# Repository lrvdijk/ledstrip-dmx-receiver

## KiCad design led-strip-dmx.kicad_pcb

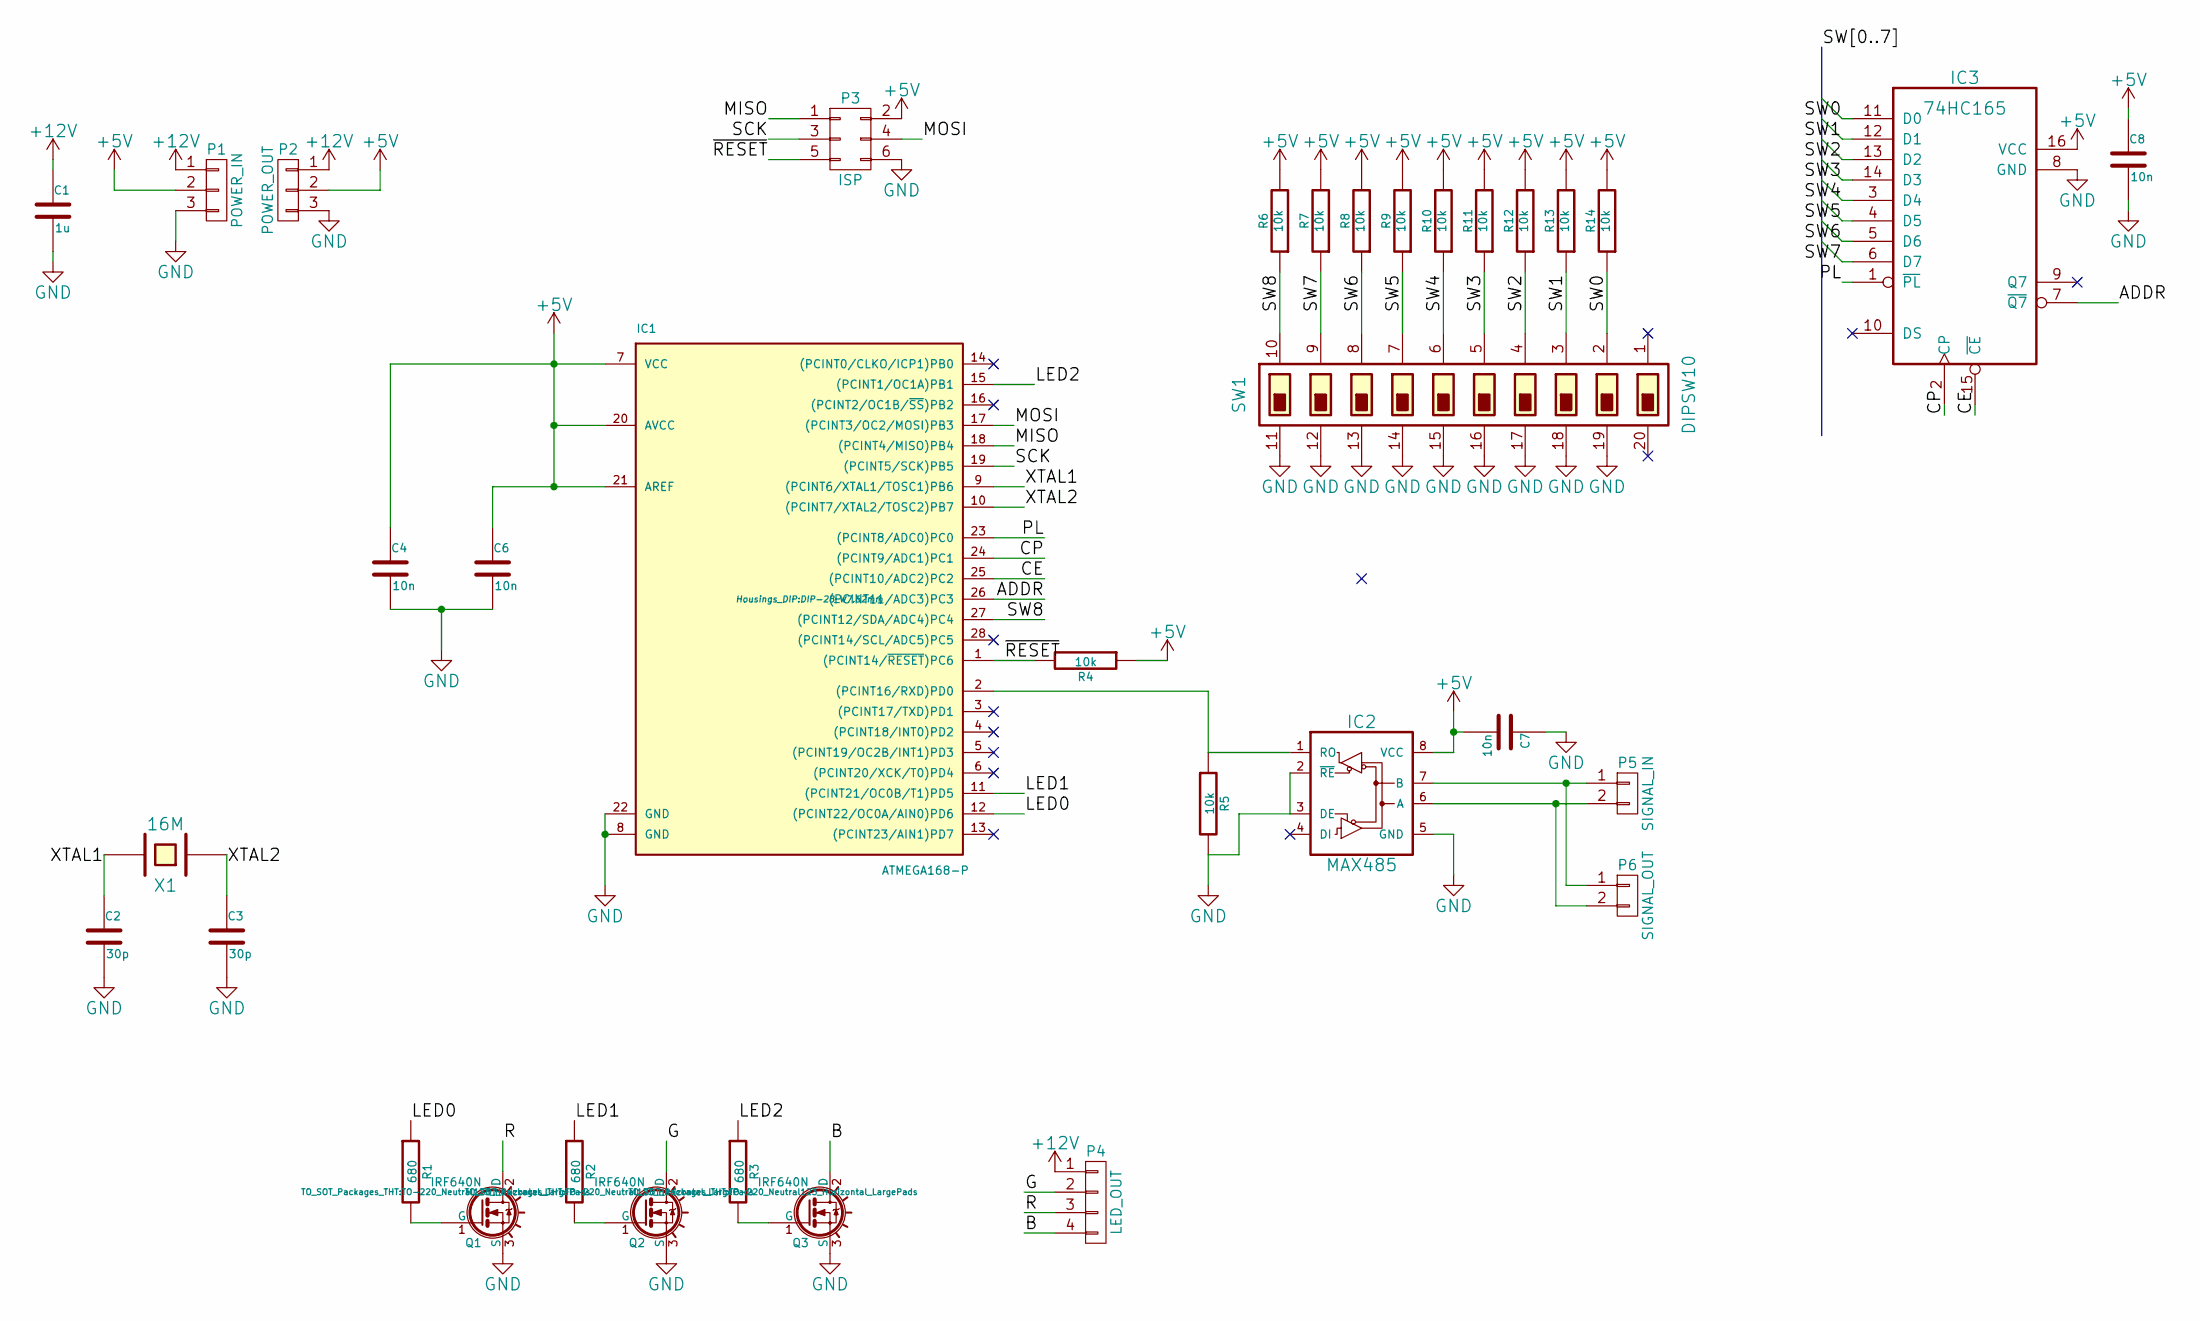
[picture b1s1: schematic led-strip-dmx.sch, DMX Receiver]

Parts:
C1: 1u; Elko_vert_11.2x6.3mm_RM2.5
C2, C3: 30p; C_Disc_D3_P2.5
C4, C6, C7, C8: 10n; C_Disc_D3_P2.5
IC1: ATMEGA168-P; DIP-28_W7.62mm
IC2: MAX485; DIP-8_W7.62mm
IC3: 74HC165; DIP-16_W7.62mm
P1: POWER_IN; Pin_Header_Straight_1x03
P2: POWER_OUT; Pin_Header_Straight_1x03
P3: ISP; Pin_Header_Straight_2x03
P4: LED_OUT; pin_strip_2mm_4
P5: SIGNAL_IN; Pin_Header_Straight_2x01
P6: SIGNAL_OUT; Pin_Header_Straight_2x01
Q1, Q2, Q3: IRF640N; TO-220_Neutral123_Horizontal_LargePads
R1, R2, R3: 680; Resistor_Horizontal_RM10mm
R4, R5, R6, R7, R8, R9, R10, R11, R12, R13, R14: 10k; Resistor_Horizontal_RM10mm
SW1: DIPSW10; DIP-20_W7.62mm
X1: 16M; HC-49V

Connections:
+5V: C4.1, C6.1, C7.2, C8.1, IC1.7 (VCC), IC1.20 (AVCC), IC1.21 (AREF), IC2.8 (VCC), IC3.16 (VCC), P1.2, P2.2, P3.2, R4.1, R6.2, R7.2, R8.2, R9.2, R10.2, R11.2, R12.2, R13.2, R14.2
+12V: C1.1, P1.1, P2.1, P4.1
/ADDR: IC1.26 ((PCINT11/ADC3)PC3), IC3.7 (~Q7)
/B: P4.4, Q3.2 (D)
/CE: IC1.25 ((PCINT10/ADC2)PC2), IC3.15 (~CE)
/CP: IC1.24 ((PCINT9/ADC1)PC1), IC3.2 (CP)
/G: P4.2, Q2.2 (D)
/LED0: IC1.12 ((PCINT22/OC0A/AIN0)PD6), R1.1
/LED1: IC1.11 ((PCINT21/OC0B/T1)PD5), R2.1
/LED2: IC1.15 ((PCINT1/OC1A)PB1), R3.1
/MISO: IC1.18 ((PCINT4/MISO)PB4), P3.1
/MOSI: IC1.17 ((PCINT3/OC2/MOSI)PB3), P3.4
/PL: IC1.23 ((PCINT8/ADC0)PC0), IC3.1 (~PL)
/R: P4.3, Q1.2 (D)
/SCK: IC1.19 ((PCINT5/SCK)PB5), P3.3
/SW0: IC3.11 (D0), R14.1, SW1.2
/SW1: IC3.12 (D1), R13.1, SW1.3
/SW2: IC3.13 (D2), R12.1, SW1.4
/SW3: IC3.14 (D3), R11.1, SW1.5
/SW4: IC3.3 (D4), R10.1, SW1.6
/SW5: IC3.4 (D5), R9.1, SW1.7
/SW6: IC3.5 (D6), R8.1, SW1.8
/SW7: IC3.6 (D7), R7.1, SW1.9
/SW8: IC1.27 ((PCINT12/SDA/ADC4)PC4), R6.1, SW1.10
/XTAL1: C2.1, IC1.9 ((PCINT6/XTAL1/TOSC1)PB6), X1.2
/XTAL2: C3.1, IC1.10 ((PCINT7/XTAL2/TOSC2)PB7), X1.1
/~RESET: IC1.1 ((PCINT14/~RESET~)PC6), P3.5, R4.2
GND: C1.2, C2.2, C3.2, C4.2, C6.2, C7.1, C8.2, IC1.8 (GND), IC1.22 (GND), IC2.2 (~RE), IC2.3 (DE), IC2.5 (GND), IC3.8 (GND), P1.3, P2.3, P3.6, Q1.3 (S), Q2.3 (S), Q3.3 (S), R5.2, SW1.11, SW1.12, SW1.13, SW1.14, SW1.15, SW1.16, SW1.17, SW1.18, SW1.19
unnamed: IC1.2 ((PCINT16/RXD)PD0), IC2.1 (RO), R5.1
unnamed: IC2.6 (A), P5.2, P6.2
unnamed: IC2.7 (B), P5.1, P6.1
unnamed: Q1.1 (G), R1.2
unnamed: Q2.1 (G), R2.2
unnamed: Q3.1 (G), R3.2

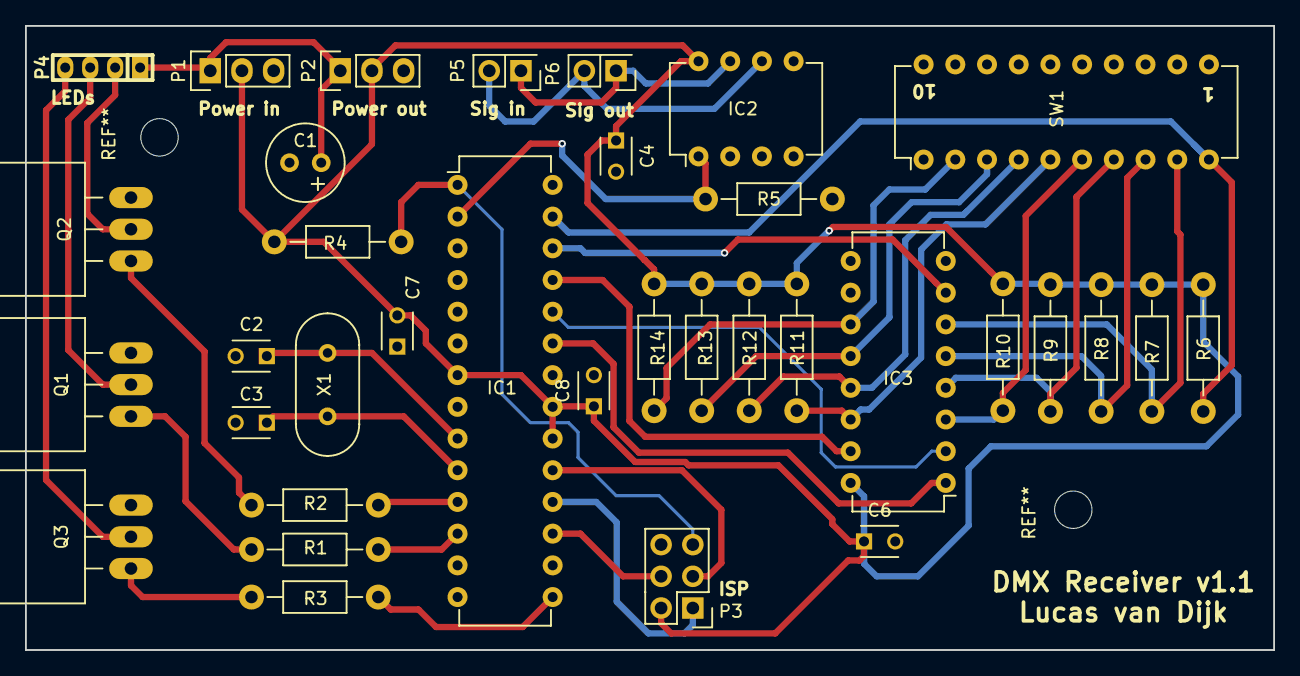
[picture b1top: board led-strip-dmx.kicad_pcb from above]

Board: 2 copper layers, 100.0 x 50.0 mm, 35 parts (0 on the bottom side), 34 nets.

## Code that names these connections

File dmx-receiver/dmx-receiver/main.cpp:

#include <stdint.h>
#include <avr/io.h>
#include <avr/interrupt.h>

#include "74hc165.h"
#include "dmx.h"

#define BAUD 250000
#define DMX_UBBR F_CPU/16/BAUD-1

// Four channels: master, R, G, B
#define DMX_CHANNELS 4

volatile uint16_t dmxAddress = 0;
volatile DmxState dmxState = IDLE;
volatile uint8_t dmxData[DMX_CHANNELS];

volatile uint8_t red = 0;
volatile uint8_t green = 0;
volatile uint8_t blue = 0;


int main() {

    // Temporarily disable interrupts
    cli();

    // Configure PWM ports as output
    DDRB = (1 << PB1);
    DDRD = (1 << PD5) | (1 << PD6);

    // 74HC165 control lines as output
    DDRC = (1 << PC0) | (1 << PC1) | (1 << PC2);

    // We use the two timers for PWM outputs
    // Setup timer 0
    // 8 bit fast PWM, non-inverting output on OC0A and OC0B, clock pre-scaler of 8
    // Enable overflow interrupt
    TCCR0A = (1 << COM0A1) | (1 << COM0B1) | (1 << WGM01) | (1 << WGM00);
    TCCR0B = (1 << CS01);
    TIMSK0 = (1 << TOIE0);

    // Setup timer 1 (16 bit timer)
    // 8 bit fast PWM, non-inverting output on OC1A, clock pre-scaler of 8
    // Enable overflow interrupt
    TCCR1A = (1 << COM1A1) | (1 << WGM12) | (1 << WGM10);
    TCCR1B = (1 << CS11);
    TIMSK1 = (1 << TOIE1);


    for(int i = 0; i < DMX_CHANNELS; i++) {
        dmxData[i] = 0;
    }

    // Initialize UART for DMX receiver
    init_uart(DMX_UBBR);

    // Enable interrupts again
    sei();
    uint8_t switch1 = 0;
    uint8_t switches = 0;

    while(true) {
        load_data_74hc165();
        switch1 = (PINC & (1 << PC4)) == 0 ? 1 : 0;
        switches = read_byte_74hc165();

        dmxAddress = (switches << 1) | switch1;

        // Calculate the pulse widths
        uint8_t master = dmxData[0];
        if(master < 255) {
            red = ((uint16_t) dmxData[1] * master) / 255;
            green = ((uint16_t) dmxData[2] * master) / 255;
            blue = ((uint16_t) dmxData[3] * master) / 255;
        } else {
            red = dmxData[1];
            green = dmxData[2];
            blue = dmxData[3];
        }
    }

    return 0;
}

ISR(USART_RX_vect) {
    // 8 bits int, use extra bool to denote first 256 or last 256 of
    // 512 possible DMX channels
    static uint16_t channelCounter = 0;

    uint8_t status = UCSR0A;
    uint8_t data = UDR0;
    uint8_t state = (uint8_t) dmxState; // Read once from SRAM

    if(status & (1 << FE0)) {
        channelCounter = 0;
        dmxState = BREAK;
        return;
    }

    // Invalid state, wait for next break
    if(status & (1 << DOR0)) {
        channelCounter = 0;
        dmxState = IDLE;
        return;
    }

    if(state == BREAK) {
        // data is now the start code, we only accept a zero start code
        if(data == 0) {
            dmxState = CHANNELS;
        } else {
            dmxState = IDLE;
        }
    } else if(state == CHANNELS) {
        if(channelCounter >= dmxAddress && channelCounter < dmxAddress+DMX_CHANNELS) {
            uint8_t index = channelCounter - dmxAddress;
            dmxData[index] = data;
        }

        if(channelCounter >= dmxAddress+DMX_CHANNELS) {
            dmxState = IDLE;
        } else {
            channelCounter++;
        }
    }
}

ISR(TIMER0_OVF_vect) {
    OCR0A = red;
    OCR0B = green;
}

ISR(TIMER1_OVF_vect) {
    OCR1A = blue;
}

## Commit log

2015-11-03 Add schematics for DMX Receiver
2015-11-03 Add components cache
2015-11-03 Add PCB design
2015-11-03 Update ignore file
2016-02-02 Fix a few major issues on the PCB
    - Used wrong pin order for LED transistors
    - Right half of the PCB did not get any power
2016-02-02 Start with the AVR C source code
    Currently it contains functions to read the 74HC165 shift
    register.
2016-02-02 Ignore Jetbrains IDE configutation
2016-02-08 Finished DMX receiver code
2016-09-26 Only read address at boot
2016-10-29 Small restructuring of dmx state machine
2016-10-29 Increase clock pre-scaling for PWM
2016-10-29 Set OCRXX registers om timer overflow
    Possible fix for flickering led strips. Also increase startup time
    of the AVR.
2016-10-29 update comments
